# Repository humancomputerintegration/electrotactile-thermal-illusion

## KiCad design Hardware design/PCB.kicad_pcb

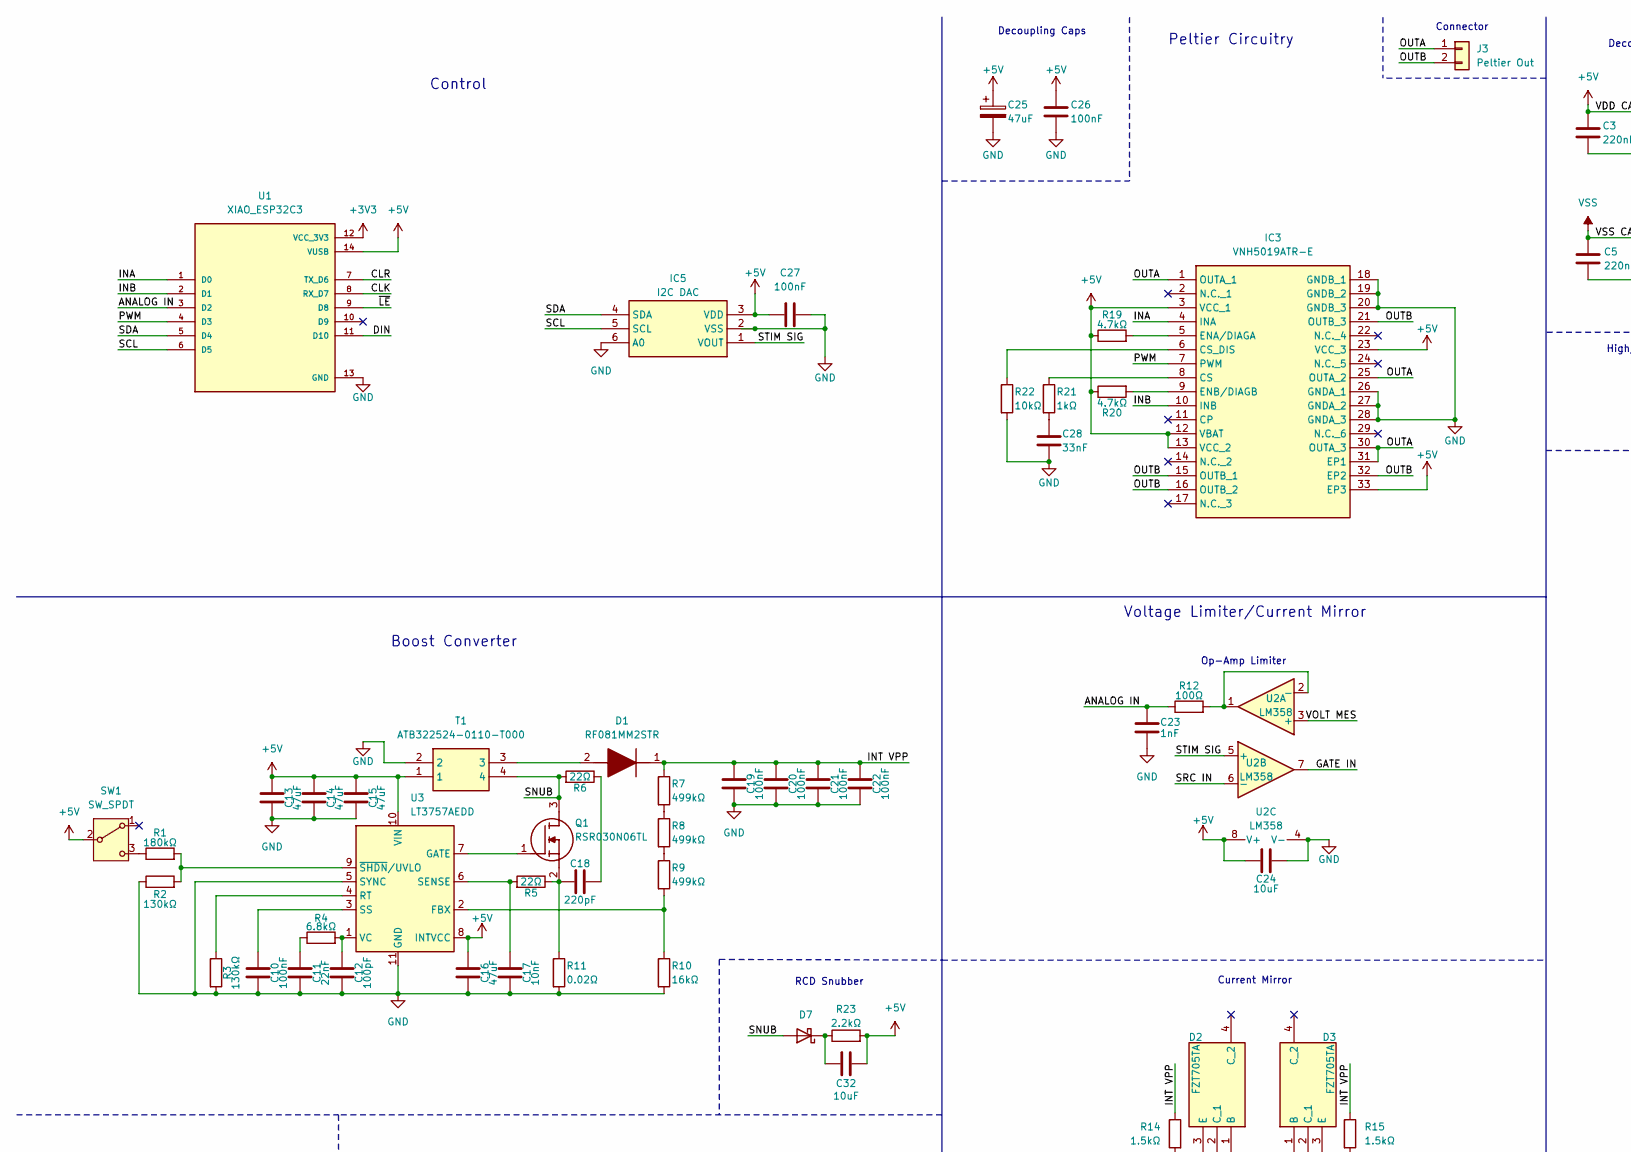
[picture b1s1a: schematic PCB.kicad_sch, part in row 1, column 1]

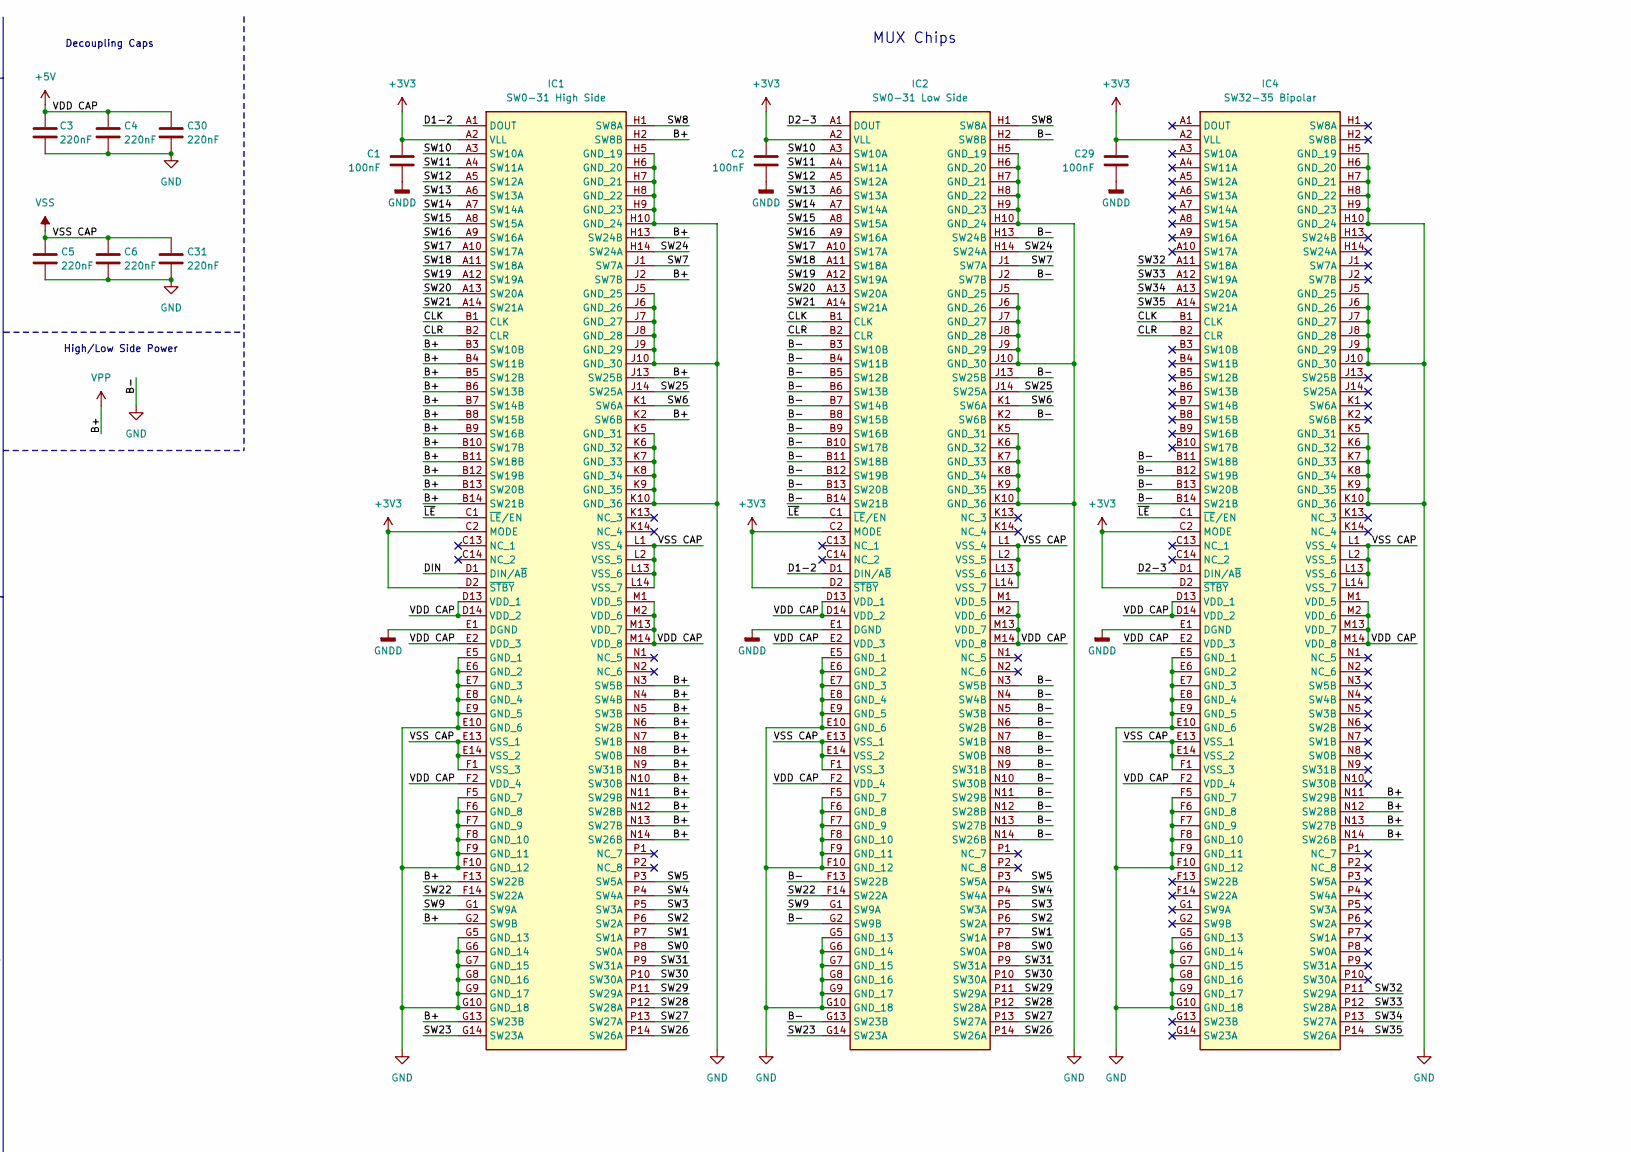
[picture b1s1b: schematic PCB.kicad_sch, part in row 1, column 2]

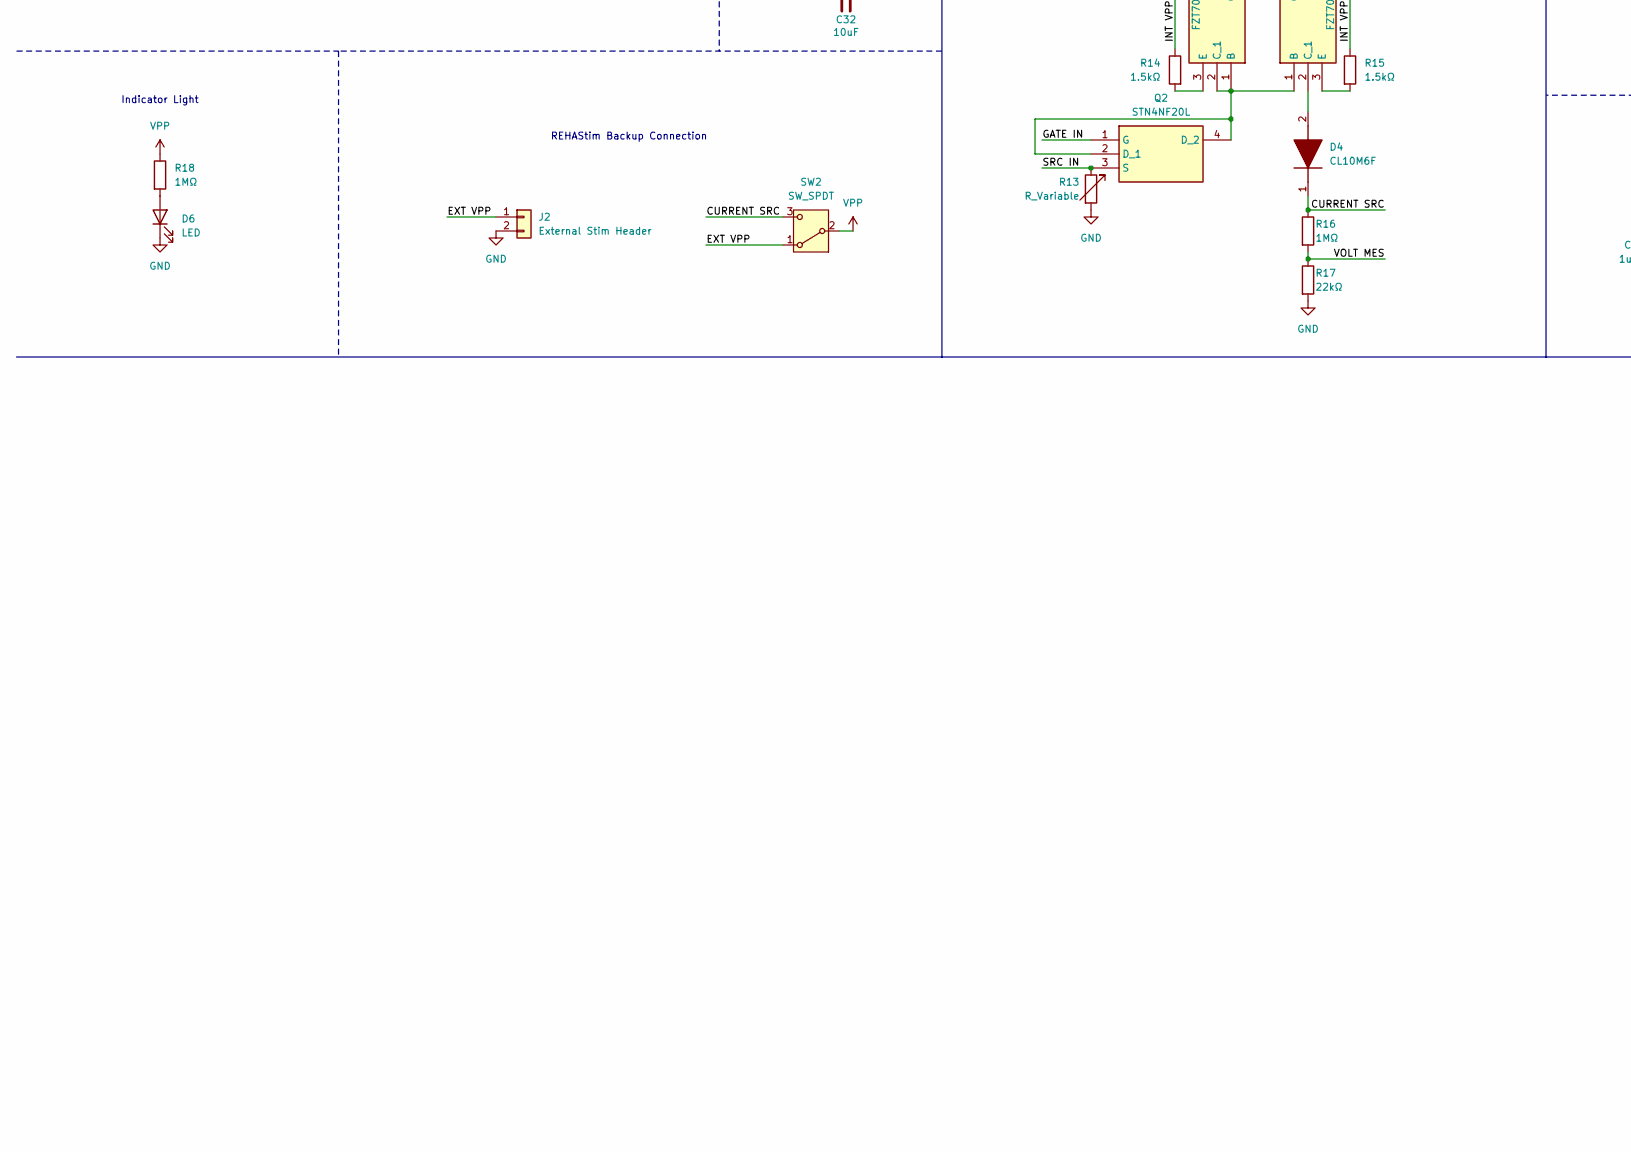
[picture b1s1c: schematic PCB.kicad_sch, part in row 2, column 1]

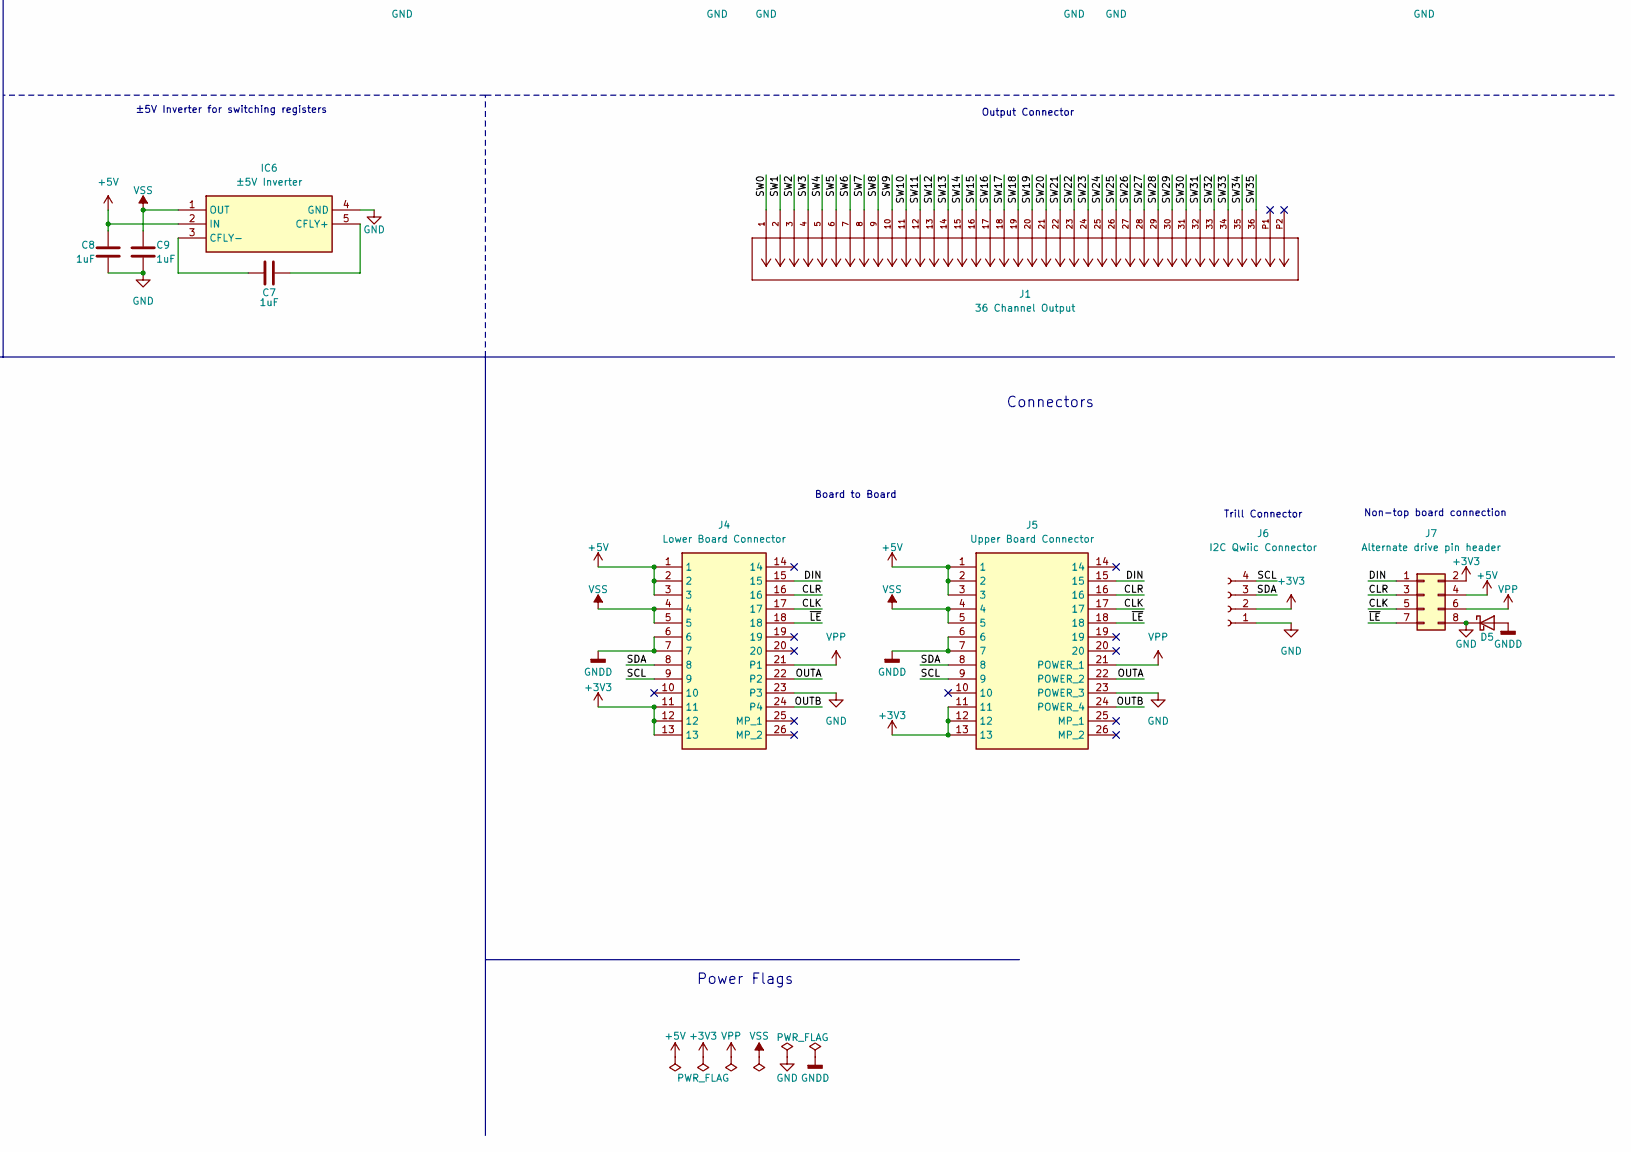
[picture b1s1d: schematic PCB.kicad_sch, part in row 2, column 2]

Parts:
C1, C2, C10, C27, C29: 100nF; C_0402_1005Metric
C3, C4, C5, C6, C30, C31: 220nF; C_0402_1005Metric
C7, C8, C9: 1uF; C_0402_1005Metric
C11: 22nF; C_0402_1005Metric
C12: 100pF; C_0402_1005Metric
C13, C14, C15, C16: 47uF; C_1206_3216Metric
C17: 10nF; C_0402_1005Metric
C18: 220pF; C_0402_1005Metric
C19, C20, C21, C22: 100nF; C_0805_2012Metric
C23: 1nF; C_0402_1005Metric
C24: 10uF; C_0805_2012Metric
C25: 47uF; CP_Elec_6.3x5.4
C26: 100nF; C_0603_1608Metric
C28: 33nF; C_0402_1005Metric
C32: 10uF; C_0603_1608Metric
D1: RF081MM2STR; Mouser Part Number 755-RF081MM2STR
D2, D3: FZT705TA; SOT230P700X170-4N; Mouser Part Number 522-FZT705TA
D4: CL10M6F; SODFL3718X130N; Mouser Part Number 637-CL05M6F
D5: GNDD Diode; D_0603_1608Metric
D6: LED; LED_0603_1608Metric
D7: D_0603_1608Metric
IC1: SW0-31 High Side; BGA132C80P14X14_1200X1200X120; Mouser Part Number 579-HV2803/AHA
IC2: SW0-31 Low Side; BGA132C80P14X14_1200X1200X120; Mouser Part Number 579-HV2803/AHA
IC3: VNH5019ATR-E; VNH5019A-E_1; Mouser Part Number 511-VNH5019ATR-E
IC4: SW32-35 Bipolar; BGA132C80P14X14_1200X1200X120; Mouser Part Number 579-HV2803/AHA
IC5: I2C DAC; SOT95P280X145-6N; Mouser Part Number 579-MCP4725A1T-E/CH
IC6: ±5V Inverter; SOT95P280X145-5N; Mouser Part Number 595-TPS60403DBVRG4
J1: 36 Channel Output; CON_5051103691_MOL; MANUFACTURER_PART_NUMBER 5051103691
J2: External Stim Header; PinHeader_1x02_P2.54mm_Vertical
J3: Peltier Out; Peltier Pads
J4: Lower Board Connector; B3241B7L111220E100; Manufacturer_Part_Number B3241B7L111220E100
J5: Upper Board Connector; B3291B7L111220E100; Manufacturer_Part_Number B3291B7L111220E100
J6: I2C Qwiic Connector; JST_SH_BM04B-SRSS-TB_1x04-1MP_P1.00mm_Vertical
J7: Alternate drive pin header; PinHeader_2x04_P2.54mm_Vertical
Q1: RSR030N06TL; SOTFL40P120X55-3N; Mouser Part Number 755-RSM002N06T2L
Q2: STN4NF20L; SOT230P700X190-4N; Mouser Part Number 511-STN4NF20L
R1: 180kΩ; R_0402_1005Metric
R2, R3: 130kΩ; R_0402_1005Metric
R4: 6.8kΩ; R_0402_1005Metric
R5, R6: 22Ω; R_0402_1005Metric
R7, R8, R9: 499kΩ; R_0402_1005Metric
R10: 16kΩ; R_0402_1005Metric
R11: 0.02Ω; R_0603_1608Metric
R12: 100Ω; R_0402_1005Metric
R13: R_Variable; Potentiometer_Bourns_3314J_Vertical
R14, R15: 1.5kΩ; R_0603_1608Metric
R16, R18: 1MΩ; R_0603_1608Metric
R17: 22kΩ; R_0603_1608Metric
R19, R20: 4.7kΩ; R_0402_1005Metric
R21: 1kΩ; R_0402_1005Metric
R22: 10kΩ; R_0402_1005Metric
R23: 2.2kΩ; R_0603_1608Metric
SW1, SW2: SW_SPDT; SW_SPDT_PCM12
T1: ATB322524-0110-T000; CHOKE_524-0110-T000_TDK-M
U1: XIAO_ESP32C3; XIAO-ESP32-C3-SMD; PARTREV 23/05/2022
U2: LM358; VSSOP-8_3x3mm_P0.65mm
U3: LT3757AEDD; DFN-10-1EP_3x3mm_P0.5mm_EP1.55x2.48mm

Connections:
+3V3: C1.1, C2.1, C29.1, IC1.A2 (VLL), IC1.C2 (MODE), IC1.D2 (~STBY), IC2.A2 (VLL), IC2.C2 (MODE), IC2.D2 (~STBY), IC4.A2 (VLL), IC4.C2 (MODE), IC4.D2 (~STBY), J4.11, J4.12, J4.13, J5.11, J5.12, J5.13, J6.2, J7.2, U1.12 (VCC_3V3)
+5V: C3.1, C4.1, C8.1, C13.1, C14.1, C15.1, C16.1, C24.1, C25.1, C26.1, C27.1, C30.1, C32.2, IC1.D13 (VDD_1), IC1.D14 (VDD_2), IC1.E2 (VDD_3), IC1.F2 (VDD_4), IC1.M1 (VDD_5), IC1.M2 (VDD_6), IC1.M13 (VDD_7), IC1.M14 (VDD_8), IC2.D13 (VDD_1), IC2.D14 (VDD_2), IC2.E2 (VDD_3), IC2.F2 (VDD_4), IC2.M1 (VDD_5), IC2.M2 (VDD_6), IC2.M13 (VDD_7), IC2.M14 (VDD_8), IC3.3 (VCC_1), IC3.12 (VBAT), IC3.13 (VCC_2), IC3.23 (VCC_3), IC3.33 (EP3), IC4.D13 (VDD_1), IC4.D14 (VDD_2), IC4.E2 (VDD_3), IC4.F2 (VDD_4), IC4.M1 (VDD_5), IC4.M2 (VDD_6), IC4.M13 (VDD_7), IC4.M14 (VDD_8), IC5.3 (VDD), IC6.2 (IN), J4.1, J4.2, J4.3, J5.1, J5.2, J5.3, J7.4, R19.1, R20.1, R23.2, SW1.2 (B), T1.1, U1.14 (VUSB), U2.8 (V+), U3.8 (INTVCC), U3.10 (VIN)
/ANALOG IN: C23.1, R12.1, U1.3 (D2)
/CLK: IC1.B1 (CLK), IC2.B1 (CLK), IC4.B1 (CLK), J4.17, J5.17, J7.5, U1.8 (RX_D7)
/CLR: IC1.B2 (CLR), IC2.B2 (CLR), IC4.B2 (CLR), J4.16, J5.16, J7.3, U1.7 (TX_D6)
/CURRENT SRC: D4.1 (K), R16.1, SW2.3 (C)
/D1-2: IC1.A1 (DOUT), IC2.D1 (DIN/A~B)
/D2-3: IC2.A1 (DOUT), IC4.D1 (DIN/A~B)
/DIN: IC1.D1 (DIN/A~B), J4.15, J5.15, J7.1, U1.11 (D10)
/EXT VPP: J2.1, SW2.1 (A)
/GATE IN: Q2.1 (G), U2.7
/INA: IC3.4 (INA), U1.1 (D0)
/INB: IC3.10 (INB), U1.2 (D1)
/INT VPP: C19.1, C20.1, C21.1, C22.1, D1.1 (K), R7.1, R14.1, R15.1
/OUTA: IC3.1 (OUTA_1), IC3.25 (OUTA_2), IC3.30 (OUTA_3), IC3.31 (EP1), J3.1, J4.22 (P2), J5.22 (POWER_2)
/OUTB: IC3.15 (OUTB_1), IC3.16 (OUTB_2), IC3.21 (OUTB_3), IC3.32 (EP2), J3.2, J4.24 (P4), J5.24 (POWER_4)
/PWM: IC3.7 (PWM), U1.4 (D3)
/SCL: IC5.5 (SCL), J4.9, J5.9, J6.4, U1.6 (D5); also elsewhere on the board
/SDA: IC5.4 (SDA), J4.8, J5.8, J6.3, U1.5 (D4); also elsewhere on the board
/SRC IN: Q2.3 (S), R13.1, U2.6 (-)
/STIM SIG: IC5.1 (VOUT), U2.5 (+)
/SW0: IC1.P8 (SW0A), IC2.P8 (SW0A), J1.1
/SW1: IC1.P7 (SW1A), IC2.P7 (SW1A), J1.2
/SW2: IC1.P6 (SW2A), IC2.P6 (SW2A), J1.3
/SW3: IC1.P5 (SW3A), IC2.P5 (SW3A), J1.4
/SW4: IC1.P4 (SW4A), IC2.P4 (SW4A), J1.5
/SW5: IC1.P3 (SW5A), IC2.P3 (SW5A), J1.6
/SW6: IC1.K1 (SW6A), IC2.K1 (SW6A), J1.7
/SW7: IC1.J1 (SW7A), IC2.J1 (SW7A), J1.8
/SW8: IC1.H1 (SW8A), IC2.H1 (SW8A), J1.9
/SW9: IC1.G1 (SW9A), IC2.G1 (SW9A), J1.10
/SW10: IC1.A3 (SW10A), IC2.A3 (SW10A), J1.11
/SW11: IC1.A4 (SW11A), IC2.A4 (SW11A), J1.12
/SW12: IC1.A5 (SW12A), IC2.A5 (SW12A), J1.13
/SW13: IC1.A6 (SW13A), IC2.A6 (SW13A), J1.14
/SW14: IC1.A7 (SW14A), IC2.A7 (SW14A), J1.15
/SW15: IC1.A8 (SW15A), IC2.A8 (SW15A), J1.16
/SW16: IC1.A9 (SW16A), IC2.A9 (SW16A), J1.17
/SW17: IC1.A10 (SW17A), IC2.A10 (SW17A), J1.18
/SW18: IC1.A11 (SW18A), IC2.A11 (SW18A), J1.19
/SW19: IC1.A12 (SW19A), IC2.A12 (SW19A), J1.20
/SW20: IC1.A13 (SW20A), IC2.A13 (SW20A), J1.21
/SW21: IC1.A14 (SW21A), IC2.A14 (SW21A), J1.22
/SW22: IC1.F14 (SW22A), IC2.F14 (SW22A), J1.23
/SW23: IC1.G14 (SW23A), IC2.G14 (SW23A), J1.24
/SW24: IC1.H14 (SW24A), IC2.H14 (SW24A), J1.25
/SW25: IC1.J14 (SW25A), IC2.J14 (SW25A), J1.26
/SW26: IC1.P14 (SW26A), IC2.P14 (SW26A), J1.27
/SW27: IC1.P13 (SW27A), IC2.P13 (SW27A), J1.28
/SW28: IC1.P12 (SW28A), IC2.P12 (SW28A), J1.29
/SW29: IC1.P11 (SW29A), IC2.P11 (SW29A), J1.30
/SW30: IC1.P10 (SW30A), IC2.P10 (SW30A), J1.31
/SW31: IC1.P9 (SW31A), IC2.P9 (SW31A), J1.32
/SW32: IC4.A11 (SW18A), IC4.P11 (SW29A), J1.33
/SW33: IC4.A12 (SW19A), IC4.P12 (SW28A), J1.34
/SW34: IC4.A13 (SW20A), IC4.P13 (SW27A), J1.35
/SW35: IC4.A14 (SW21A), IC4.P14 (SW26A), J1.36
/VOLT MES: R16.2, R17.1, U2.3 (+)
/~LE: IC1.C1 (~LE/EN), IC2.C1 (~LE/EN), IC4.C1 (~LE/EN), J4.18, J5.18, J7.7, U1.9 (D8)
GND: C3.2, C4.2, C5.2, C6.2, C8.2, C9.2, C10.2, C11.2, C12.2, C13.2, C14.2, C15.2, C16.2, C17.2, C19.2, C20.2, C21.2, C22.2, C23.2, C24.2, C25.2, C26.2, C27.2, C28.2, C30.2, C31.2, D5.1 (K), D6.1 (K), IC1.E5 (GND_1), IC1.E6 (GND_2), IC1.E7 (GND_3), IC1.E8 (GND_4), IC1.E9 (GND_5), IC1.E10 (GND_6), IC1.F5 (GND_7), IC1.F6 (GND_8), IC1.F7 (GND_9), IC1.F8 (GND_10), IC1.F9 (GND_11), IC1.F10 (GND_12), IC1.G5 (GND_13), IC1.G6 (GND_14), IC1.G7 (GND_15), IC1.G8 (GND_16), IC1.G9 (GND_17), IC1.G10 (GND_18), IC1.H5 (GND_19), IC1.H6 (GND_20), IC1.H7 (GND_21), IC1.H8 (GND_22), IC1.H9 (GND_23), IC1.H10 (GND_24), IC1.J5 (GND_25), IC1.J6 (GND_26), IC1.J7 (GND_27), IC1.J8 (GND_28), IC1.J9 (GND_29), IC1.J10 (GND_30), IC1.K5 (GND_31), IC1.K6 (GND_32), IC1.K7 (GND_33), IC1.K8 (GND_34), IC1.K9 (GND_35), IC1.K10 (GND_36), IC2.B3 (SW10B), IC2.B4 (SW11B), IC2.B5 (SW12B), IC2.B6 (SW13B), IC2.B7 (SW14B), IC2.B8 (SW15B), IC2.B9 (SW16B), IC2.B10 (SW17B), IC2.B11 (SW18B), IC2.B12 (SW19B), IC2.B13 (SW20B), IC2.B14 (SW21B), IC2.E5 (GND_1), IC2.E6 (GND_2), IC2.E7 (GND_3), IC2.E8 (GND_4), IC2.E9 (GND_5), IC2.E10 (GND_6), IC2.F5 (GND_7), IC2.F6 (GND_8), IC2.F7 (GND_9), IC2.F8 (GND_10), IC2.F9 (GND_11), IC2.F10 (GND_12), IC2.F13 (SW22B), IC2.G2 (SW9B), IC2.G5 (GND_13), IC2.G6 (GND_14), IC2.G7 (GND_15), IC2.G8 (GND_16), IC2.G9 (GND_17), IC2.G10 (GND_18), IC2.G13 (SW23B), IC2.H2 (SW8B), IC2.H5 (GND_19), IC2.H6 (GND_20), IC2.H7 (GND_21), IC2.H8 (GND_22), IC2.H9 (GND_23), IC2.H10 (GND_24), IC2.H13 (SW24B), IC2.J2 (SW7B), IC2.J5 (GND_25), IC2.J6 (GND_26), IC2.J7 (GND_27), IC2.J8 (GND_28), IC2.J9 (GND_29), IC2.J10 (GND_30), IC2.J13 (SW25B), IC2.K2 (SW6B), IC2.K5 (GND_31), IC2.K6 (GND_32), IC2.K7 (GND_33), IC2.K8 (GND_34), IC2.K9 (GND_35), IC2.K10 (GND_36), IC2.N3 (SW5B), IC2.N4 (SW4B), IC2.N5 (SW3B), IC2.N6 (SW2B), IC2.N7 (SW1B), IC2.N8 (SW0B), IC2.N9 (SW31B), IC2.N10 (SW30B), IC2.N11 (SW29B), IC2.N12 (SW28B), IC2.N13 (SW27B), IC2.N14 (SW26B), IC3.18 (GNDB_1), IC3.19 (GNDB_2), IC3.20 (GNDB_3), IC3.26 (GNDA_1), IC3.27 (GNDA_2), IC3.28 (GNDA_3), IC4.B11 (SW18B), IC4.B12 (SW19B), IC4.B13 (SW20B), IC4.B14 (SW21B), IC4.E5 (GND_1), IC4.E6 (GND_2), IC4.E7 (GND_3), IC4.E8 (GND_4), IC4.E9 (GND_5), IC4.E10 (GND_6), IC4.F5 (GND_7), IC4.F6 (GND_8), IC4.F7 (GND_9), IC4.F8 (GND_10), IC4.F9 (GND_11), IC4.F10 (GND_12), IC4.G5 (GND_13), IC4.G6 (GND_14), IC4.G7 (GND_15), IC4.G8 (GND_16), IC4.G9 (GND_17), IC4.G10 (GND_18), IC4.H5 (GND_19), IC4.H6 (GND_20), IC4.H7 (GND_21), IC4.H8 (GND_22), IC4.H9 (GND_23), IC4.H10 (GND_24), IC4.J5 (GND_25), IC4.J6 (GND_26), IC4.J7 (GND_27), IC4.J8 (GND_28), IC4.J9 (GND_29), IC4.J10 (GND_30), IC4.K5 (GND_31), IC4.K6 (GND_32), IC4.K7 (GND_33), IC4.K8 (GND_34), IC4.K9 (GND_35), IC4.K10 (GND_36), IC5.2 (VSS), IC5.6 (A0), IC6.4 (GND), J2.2, J4.23 (P3), J5.23 (POWER_3), J6.1, J7.8, R2.1, R3.2, R10.2, R11.2, R13.2, R17.2, R22.2, T1.2, U1.13 (GND), U2.4 (V-), U3.5 (SYNC), U3.11 (GND); also elsewhere on the board
GNDD: C1.2, C2.2, C29.2, D5.2 (A), IC1.E1 (DGND), IC2.E1 (DGND), IC4.E1 (DGND), J4.6, J4.7, J5.6, J5.7
unnamed: C11.1, R4.1
unnamed: C18.2, R6.1
unnamed: C28.1, R21.2
unnamed: D1.2 (A), T1.3
unnamed: D2.1 (B), D2.2 (C_1), D3.1 (B), Q2.2 (D_1), Q2.4 (D_2)
unnamed: D2.3 (E), R14.2
unnamed: D3.2 (C_1), D4.2 (A)
unnamed: D3.3 (E), R15.2
unnamed: D6.2 (A), R18.2
unnamed: C32.1, D7.1 (K), R23.1
unnamed: IC3.8 (CS), R21.1
unnamed: IC3.6 (CS_DIS), R22.1
unnamed: IC3.5 (ENA/DIAGA), R19.2
unnamed: IC3.9 (ENB/DIAGB), R20.2
unnamed: C7.1, IC6.5 (CFLY+)
unnamed: C7.2, IC6.3 (CFLY-)
unnamed: Q1.1 (G), U3.7 (GATE)
unnamed: C18.1, Q1.2 (S), R5.1, R11.1
unnamed: R7.2, R8.1
unnamed: R8.2, R9.1
unnamed: R1.1, SW1.3 (C)
unnamed: R12.2, U2.1, U2.2 (-)
unnamed: R9.2, R10.1, U3.2 (FBX)
unnamed: R3.1, U3.4 (RT)
unnamed: C17.1, R5.2, U3.6 (SENSE)
unnamed: C10.1, U3.3 (SS)
unnamed: C12.1, R4.2, U3.1 (VC)
unnamed: R1.2, R2.2, U3.9 (~SHDN/UVLO)
VPP: IC1.B3 (SW10B), IC1.B4 (SW11B), IC1.B5 (SW12B), IC1.B6 (SW13B), IC1.B7 (SW14B), IC1.B8 (SW15B), IC1.B9 (SW16B), IC1.B10 (SW17B), IC1.B11 (SW18B), IC1.B12 (SW19B), IC1.B13 (SW20B), IC1.B14 (SW21B), IC1.F13 (SW22B), IC1.G2 (SW9B), IC1.G13 (SW23B), IC1.H2 (SW8B), IC1.H13 (SW24B), IC1.J2 (SW7B), IC1.J13 (SW25B), IC1.K2 (SW6B), IC1.N3 (SW5B), IC1.N4 (SW4B), IC1.N5 (SW3B), IC1.N6 (SW2B), IC1.N7 (SW1B), IC1.N8 (SW0B), IC1.N9 (SW31B), IC1.N10 (SW30B), IC1.N11 (SW29B), IC1.N12 (SW28B), IC1.N13 (SW27B), IC1.N14 (SW26B), IC4.N11 (SW29B), IC4.N12 (SW28B), IC4.N13 (SW27B), IC4.N14 (SW26B), J4.21 (P1), J5.21 (POWER_1), J7.6, R18.1, SW2.2 (B)
VSS: C5.1, C6.1, C9.1, C31.1, IC1.E13 (VSS_1), IC1.E14 (VSS_2), IC1.F1 (VSS_3), IC1.L1 (VSS_4), IC1.L2 (VSS_5), IC1.L13 (VSS_6), IC1.L14 (VSS_7), IC2.E13 (VSS_1), IC2.E14 (VSS_2), IC2.F1 (VSS_3), IC2.L1 (VSS_4), IC2.L2 (VSS_5), IC2.L13 (VSS_6), IC2.L14 (VSS_7), IC4.E13 (VSS_1), IC4.E14 (VSS_2), IC4.F1 (VSS_3), IC4.L1 (VSS_4), IC4.L2 (VSS_5), IC4.L13 (VSS_6), IC4.L14 (VSS_7), IC6.1 (OUT), J4.4, J4.5, J5.4, J5.5; also elsewhere on the board

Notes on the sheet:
Op-Amp Limiter
Current Mirror
Output Connector
Trill Connector
Connectors
Voltage Limiter/Current Mirror
Decoupling Caps
MUX Chips
±5V Inverter for switching registers
High/Low Side Power
Power Flags
Peltier Circuitry
Boost Converter
RCD Snubber
Control
Connector
Board to Board
Non-top board connection
REHAStim Backup Connection
Indicator Light

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
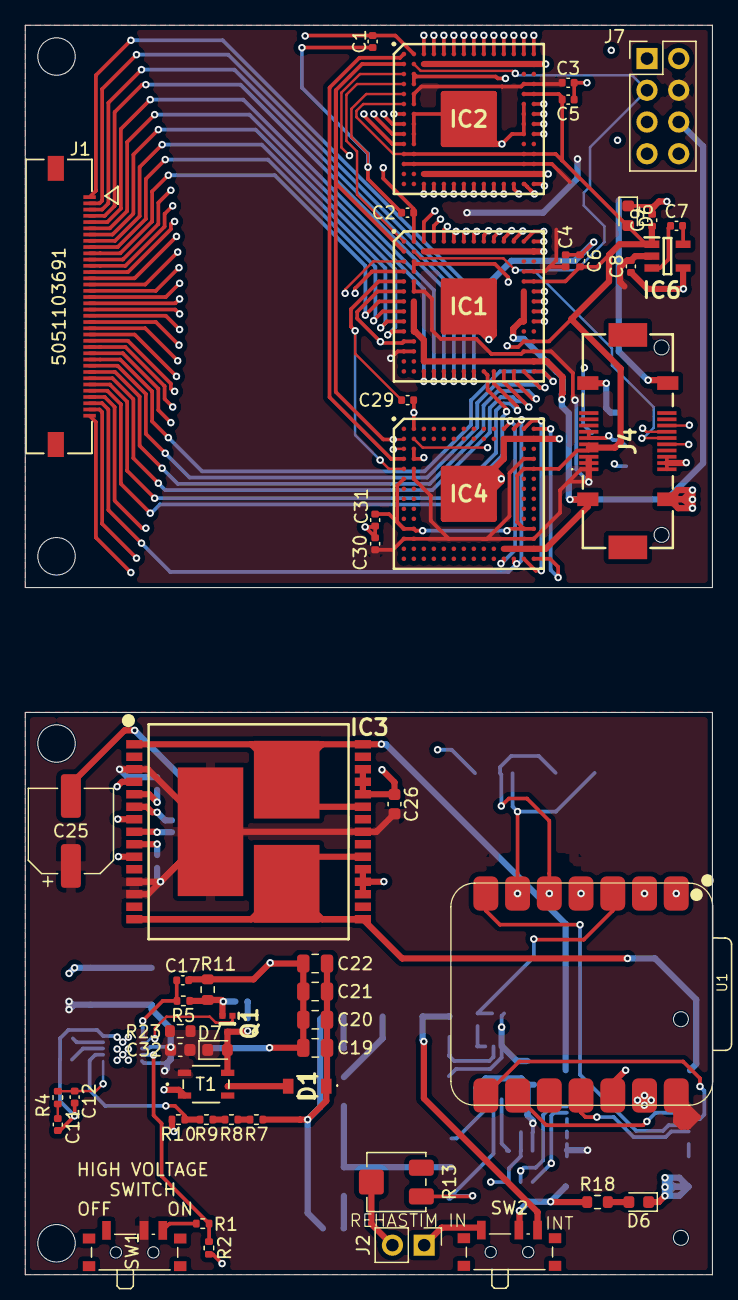
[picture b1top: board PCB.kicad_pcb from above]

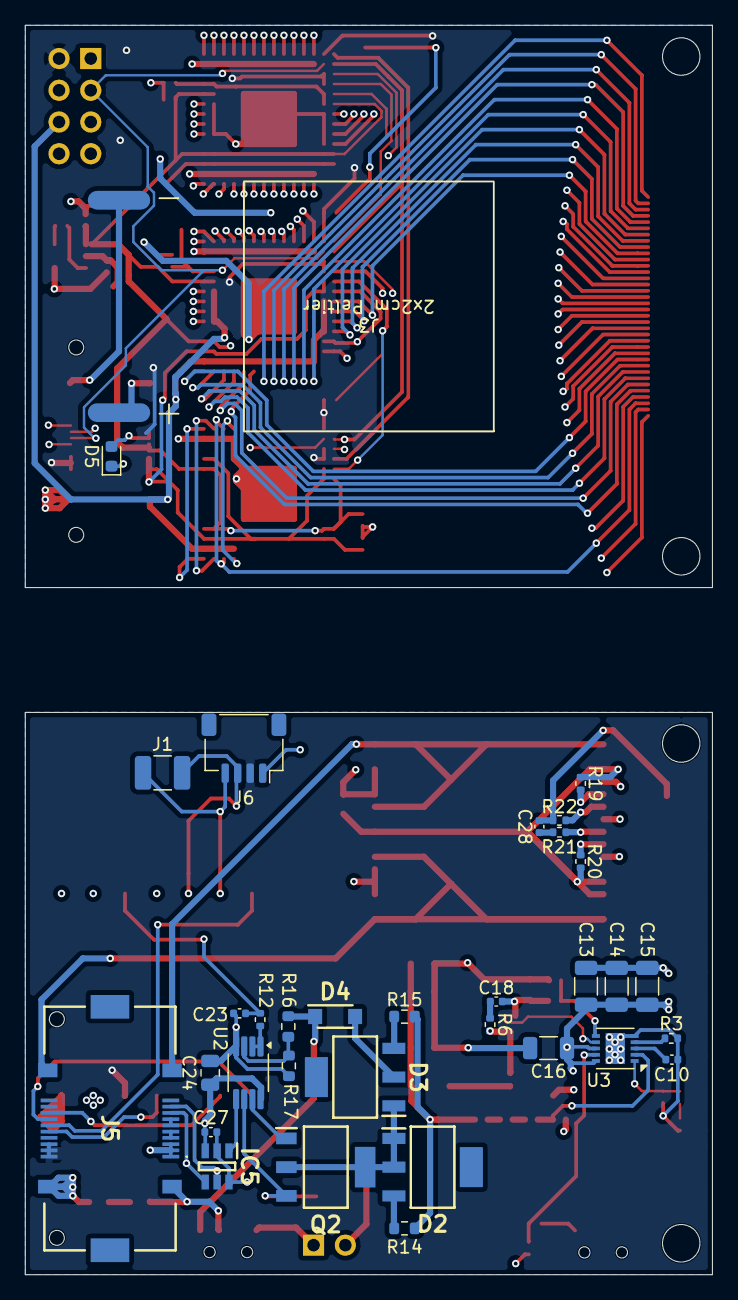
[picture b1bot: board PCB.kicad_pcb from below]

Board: 4 copper layers, 55.0 x 100.0 mm, 87 parts (33 on the bottom side), 92 nets.

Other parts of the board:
D6#2: VSS Diode; D_0603_1608Metric
J1#2: I2C Pads; C_1210_3225Metric_Pad1.33x2.70mm_HandSolder
J**: Support NPTH
J**#2: Support NPTH

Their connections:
/SCL: J1#2.1; also elsewhere on the board
/SDA: J1#2.2; also elsewhere on the board
GND: D6#2.1 (K); also elsewhere on the board
VSS: D6#2.2 (A); also elsewhere on the board

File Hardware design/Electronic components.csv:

Reference,Qty,Value,Footprint,Datasheet,Item Type
"C1,C2,C10,C27,C29",5,100nF,C_0402_1005Metric,(Generic/standardized component),Ceramic Capacitor
"C3,C4,C5,C6,C30,C31",6,220nF,C_0402_1005Metric,(Generic/standardized component),Ceramic Capacitor
"C7,C8,C9",3,1uF,C_0402_1005Metric,(Generic/standardized component),Ceramic Capacitor
C11,1,22nF,C_0402_1005Metric,(Generic/standardized component),Ceramic Capacitor
C12,1,100pF,C_0402_1005Metric,(Generic/standardized component),Ceramic Capacitor
"C13,C14,C15,C16",4,47uF,C_1206_3216Metric,(Generic/standardized component),Ceramic Capacitor
C17,1,10nF,C_0402_1005Metric,(Generic/standardized component),Ceramic Capacitor
C18,1,220pF,C_0402_1005Metric,(Generic/standardized component),Ceramic Capacitor
"C19,C20,C21,C22",4,100nF,C_0805_2012Metric,(Generic/standardized component),Ceramic Capacitor
C23,1,1nF,C_0402_1005Metric,(Generic/standardized component),Ceramic Capacitor
C24,1,10uF,C_0805_2012Metric,(Generic/standardized component),Ceramic Capacitor
C25,1,47uF,CP_Elec_6.3x5.4,(Generic/standardized component),Radial Capacitor
C26,1,100nF,C_0603_1608Metric,(Generic/standardized component),Ceramic Capacitor
C28,1,33nF,C_0402_1005Metric,(Generic/standardized component),Ceramic Capacitor
C32,1,10uF,C_0603_1608Metric,(Generic/standardized component),Ceramic Capacitor
D1,1,RF081MM2STR,RF081MM2STR,https://fscdn.rohm.com/en/products/databook/datasheet/discre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,Fast-Recovery Diode for Boosted Output
"D2,D3",2,FZT705TA,SOT230P700X170-4N,https://www.diodes.com//assets/Datasheets/FZT705.pdf,PNP Darlington Transistors
D4,1,CL20M6F,SODFL3718X130N,https://www.tme.com/html/EN/current-regulating-diodes-crd/ra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,CL20M6F Current Regulating Diode
D5,1,GNDD Diode,D_0603_1608Metric,(Generic/standardized component),Schottky Diode
D6,1,LED,LED_0603_1608Metric,(Generic/standardized component),Indicator LED
D7,1,SBD,D_0603_1608Metric,(Generic/standardized component),Schottky Diode
IC1,1,SW0-31 High Side,BGA132C80P14X14_1200X1200X120,https://ww1.microchip.com/downloads/en/DeviceDoc/HV2803-HV29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,HV2803 High-Voltage Analog Switch 
IC2,1,SW0-31 Low Side,BGA132C80P14X14_1200X1200X120,https://ww1.microchip.com/downloads/en/DeviceDoc/HV2803-HV29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,HV2803 High-Voltage Analog Switch
IC3,1,VNH5019ATR-E,VNH5019A-E_1,https://www.st.com/resource/en/datasheet/vnh5019a-e.pdf,H-Bridge
IC4,1,SW32-35 Bipolar,BGA132C80P14X14_1200X1200X120,https://ww1.microchip.com/downloads/en/DeviceDoc/HV2803-HV29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,HV2803 High-Voltage Analog Switch
IC5,1,I2C DAC,SOT95P280X145-6N,http://ww1.microchip.com/downloads/en/DeviceDoc/22039d.pdf,MCP4725 I2C DAC
IC6,1,±5V Inverter,SOT95P280X145-5N,http://www.ti.com/lit/ds/symlink/tps60403.pdf,TPS60403 Voltage Inverter
J1,1,36 Channel Output,CON_5051103691_MOL,https://www.molex.com/en-us/products/part-detail/781193620,36-pin Molex FFC FPC Connector
J2,1,External Stim Header,Connector_PinHeader_2.54mm:PinHeader_1x02_P2.54mm_Vertical,(Generic/standardized component),Generic 2.54mm pin header (1x2)
J4,1,Lower Board Connector,B3241B7L111220E100,https://cdn.amphenol-cs.com/media/wysiwyg/files/drawing/b324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,B3241B7L111220E100 BTB Connector Male 
J5,1,Upper Board Connector,B3291B7L111220E100,https://cdn.amphenol-cs.com/media/wysiwyg/files/drawing/b329.pdf,B3291B7L111220E100 BTB Connector Female 
J6,1,I2C Qwiic Connector,JST_SH_BM04B-SRSS-TB_1x04-1MP_P1.00mm_Vertical,(Generic/standardized component),4-pin JST Female Connector
Q1,1,RSR030N06TL,SOTFL40P120X55-3N,https://www.mouser.com/catalog/specsheets/rsr030n06-e-1139120.pdf,Switching MOSFET
Q2,1,STN4NF20L,SOT230P700X190-4N,https://www.st.com/resource/en/datasheet/stn4nf20l.pdf,Logic-Level MOSFET
R1,1,180kOhm,R_0402_1005Metric,(Generic/standardized component),Thick Film Resistor
"R2,R3",2,130kOhm,R_0402_1005Metric,(Generic/standardized component),Thick Film Resistor
R4,1,6.8kOhm,R_0402_1005Metric,(Generic/standardized component),Thick Film Resistor
"R5,R6",2,22Ohm,R_0402_1005Metric,(Generic/standardized component),Thick Film Resistor
"R7,R8,R9",3,499kOhm,R_0402_1005Metric,(Generic/standardized component),Thick Film Resistor
R10,1,16kOhm,R_0402_1005Metric,(Generic/standardized component),Thick Film Resistor
R11,1,0.02Ohm,R_0603_1608Metric,(Generic/standardized component),Thick Film Resistor
R12,1,100Ohm,R_0402_1005Metric,(Generic/standardized component),Thick Film Resistor
R13,1,R_Variable,Potentiometer_SMD:Potentiometer_Bourns_3314J_Vertical,(Generic/standardized component),Potentiometer
"R14,R15",2,1.5kOhm,R_0603_1608Metric,(Generic/standardized component),Thick Film Resistor
"R16,R18",2,1MOhm,R_0603_1608Metric,(Generic/standardized component),Thick Film Resistor
R17,1,22kOhm,R_0603_1608Metric,(Generic/standardized component),Thick Film Resistor
R21,1,1kOhm,R_0402_1005Metric,(Generic/standardized component),Thick Film Resistor
R22,1,10kOhm,R_0402_1005Metric,(Generic/standardized component),Thick Film Resistor
R23,1,2.2kOhm,R_0603_1608Metric,(Generic/standardized component),Thick Film Resistor
"SW1,SW2",2,SW_SPDT,SW_SPDT_PCM12,(Generic/standardized component),Single-pole Double-throw Switch
T1,1,ATB322524-0110-T000,CHOKE_524-0110-T000_TDK-M,https://4donline.ihs.com/images/VipMasterIC/IC/TDKC/TDKC-S-A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,10:1 Transformer
U1,1,XIAO_ESP32C3,XIAO-ESP32-C3-SMD,https://www.digikey.com/en/products/detail/seeed-technology-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,XIAO ESP32-C3 Board
U2,1,LM358,Package_SO:VSSOP-8_3x3mm_P0.65mm,http://www.ti.com/lit/ds/symlink/lm2904-n.pdf,LM358 Op-Amp
U3,1,LT3757AEDD,Package_DFN_QFN:DFN-10-1EP_3x3mm_P0.5mm_EP1.55x2.48mm,https://www.analog.com/media/en/technical-documentation/data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,LT3757 Boost Regulator
